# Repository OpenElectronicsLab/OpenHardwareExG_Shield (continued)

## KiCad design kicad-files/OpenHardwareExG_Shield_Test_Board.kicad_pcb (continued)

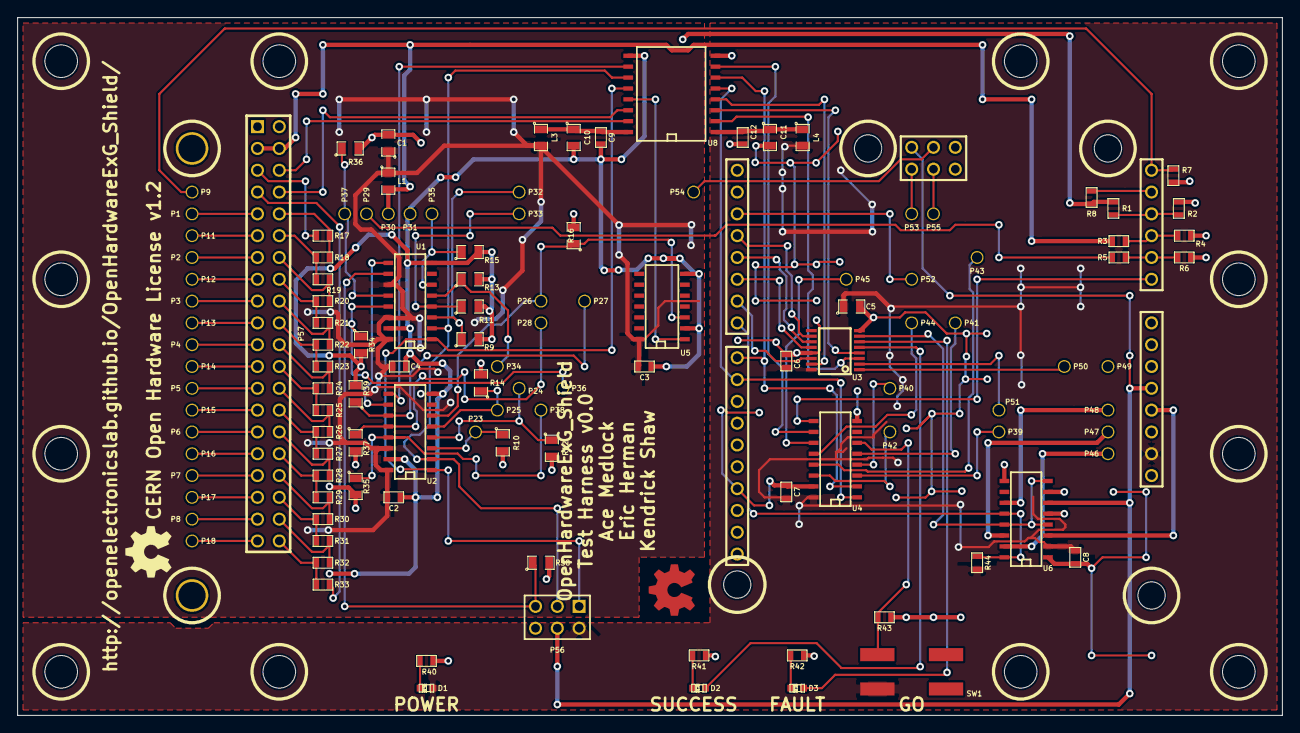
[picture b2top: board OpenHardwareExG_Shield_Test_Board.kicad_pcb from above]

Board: 4 copper layers, 147.3 x 81.3 mm, 137 parts (0 on the bottom side), 105 nets.

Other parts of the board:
Hole_M3, Hole_M3#2, Hole_M3#3, Hole_M3#4, Hole_M3#5, Hole_M3#6, Hole_M3#7, Hole_M3#8, Hole_M3#9, Hole_M3#10, Hole_M3#11, Hole_M3#12, Hole_M3#13, Hole_M3#14: VAL**; Hole_M3

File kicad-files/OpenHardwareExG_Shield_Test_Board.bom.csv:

ref,value,footprint,partnum,supplier
C1,10uF,SM0805,LMK212B7106KG-TD,mouser
C2,100nF,SM0603,VJ0603Y104JXJPW1BC,mouser
C3,100nF,SM0603,VJ0603Y104JXJPW1BC,mouser
C4,100nF,SM0603,VJ0603Y104JXJPW1BC,mouser
C5,10uF,SM0805,LMK212B7106KG-TD,mouser
C6,100nF,SM0603,VJ0603Y104JXJPW1BC,mouser
C7,100nF,SM0603,VJ0603Y104JXJPW1BC,mouser
C8,100nF,SM0603,VJ0603Y104JXJPW1BC,mouser
C9,100nF,SM0603,VJ0603Y104JXJPW1BC,mouser
C10,10uF,SM0805,LMK212B7106KG-TD,mouser
C11,10uF,SM0805,LMK212B7106KG-TD,mouser
C12,100nF,SM0603,VJ0603Y104JXJPW1BC,mouser
D1,LED,LED-0603,HT-193UYG-5592,mouser
D2,LED,LED-0603,HT-193UYG-5592,mouser
D3,LED,LED-0603,APTD1608SURCK,mouser
L1,MH2029-221Y,SM0805,MH2029-221Y,mouser
L3,MH2029-221Y,SM0805,MH2029-221Y,mouser
L4,MH2029-221Y,SM0805,MH2029-221Y,mouser
P1,CONN_1,POGO_PIN_BASE,PRT-09173,sparkfun
P2,CONN_1,POGO_PIN_BASE,PRT-09173,sparkfun
P3,CONN_1,POGO_PIN_BASE,PRT-09173,sparkfun
P4,CONN_1,POGO_PIN_BASE,PRT-09173,sparkfun
P5,CONN_1,POGO_PIN_BASE,PRT-09173,sparkfun
P6,CONN_1,POGO_PIN_BASE,PRT-09173,sparkfun
P7,CONN_1,POGO_PIN_BASE,PRT-09173,sparkfun
P8,CONN_1,POGO_PIN_BASE,PRT-09173,sparkfun
P9,CONN_1,POGO_PIN_BASE,PRT-09173,sparkfun
P11,CONN_1,POGO_PIN_BASE,PRT-09173,sparkfun
P12,CONN_1,POGO_PIN_BASE,PRT-09173,sparkfun
P13,CONN_1,POGO_PIN_BASE,PRT-09173,sparkfun
P14,CONN_1,POGO_PIN_BASE,PRT-09173,sparkfun
P15,CONN_1,POGO_PIN_BASE,PRT-09173,sparkfun
P16,CONN_1,POGO_PIN_BASE,PRT-09173,sparkfun
P17,CONN_1,POGO_PIN_BASE,PRT-09173,sparkfun
P18,CONN_1,POGO_PIN_BASE,PRT-09173,sparkfun
P19a,CONN_40x1,arduino_shield_with_holes_header,PRT-00116,sparkfun
P19b,CONN_3x2,arduino_shield_with_holes_spi,PRT-13010,sparkfun
P23,CONN_1,POGO_PIN_BASE,PRT-09173,sparkfun
P24,CONN_1,POGO_PIN_BASE,PRT-09173,sparkfun
P25,CONN_1,POGO_PIN_BASE,PRT-09173,sparkfun
P26,CONN_1,POGO_PIN_BASE,PRT-09173,sparkfun
P27,CONN_1,POGO_PIN_BASE,PRT-09173,sparkfun
P28,CONN_1,POGO_PIN_BASE,PRT-09173,sparkfun
P29,CONN_1,POGO_PIN_BASE,PRT-09173,sparkfun
P30,CONN_1,POGO_PIN_BASE,PRT-09173,sparkfun
P31,CONN_1,POGO_PIN_BASE,PRT-09173,sparkfun
P32,CONN_1,POGO_PIN_BASE,PRT-09173,sparkfun
P33,CONN_1,POGO_PIN_BASE,PRT-09173,sparkfun
P34,CONN_1,POGO_PIN_BASE,PRT-09173,sparkfun
P35,CONN_1,POGO_PIN_BASE,PRT-09173,sparkfun
P36,CONN_1,POGO_PIN_BASE,PRT-09173,sparkfun
P37,CONN_1,POGO_PIN_BASE,PRT-09173,sparkfun
P38,CONN_1,POGO_PIN_BASE,PRT-09173,sparkfun
P39,CONN_1,POGO_PIN_BASE,PRT-09173,sparkfun
P40,CONN_1,POGO_PIN_BASE,PRT-09173,sparkfun
P41,CONN_1,POGO_PIN_BASE,PRT-09173,sparkfun
P42,CONN_1,POGO_PIN_BASE,PRT-09173,sparkfun
P43,CONN_1,POGO_PIN_BASE,PRT-09173,sparkfun
P44,CONN_1,POGO_PIN_BASE,PRT-09173,sparkfun
P45,CONN_1,POGO_PIN_BASE,PRT-09173,sparkfun
P46,CONN_1,POGO_PIN_BASE,PRT-09173,sparkfun
P47,CONN_1,POGO_PIN_BASE,PRT-09173,sparkfun
P48,CONN_1,POGO_PIN_BASE,PRT-09173,sparkfun
P49,CONN_1,POGO_PIN_BASE,PRT-09173,sparkfun
P50,CONN_1,POGO_PIN_BASE,PRT-09173,sparkfun
P51,CONN_1,POGO_PIN_BASE,PRT-09173,sparkfun
P52,CONN_1,POGO_PIN_BASE,PRT-09173,sparkfun
P53,CONN_1,POGO_PIN_BASE,PRT-09173,sparkfun
P54,CONN_1,POGO_PIN_BASE,PRT-09173,sparkfun
P55,CONN_1,POGO_PIN_BASE,PRT-09173,sparkfun
P56,CONN_3X2,pin_array_3x2,PRT-12807,sparkfun
P57,CONN_20X2,PIN_ARRAY_20X2,571-2-826925-0,mouser
R1,10k,SM0603,RR0816P-103-D,mouser
R2,1k,SM0603,CRCW06031K00FKEA,mouser
R3,10k,SM0603,RR0816P-103-D,mouser
R4,1k,SM0603,CRCW06031K00FKEA,mouser
R5,10k,SM0603,RR0816P-103-D,mouser
R6,1k,SM0603,CRCW06031K00FKEA,mouser
R7,5.1k,SM0603,CRCW06035K10FKEA,mouser
R8,100,SM0603,CRCW0603100RFKEA,mouser
R9,1M,SM0805,RR1220P-105-D,mouser
R10,1M,SM0805,RR1220P-105-D,mouser
R11,1M,SM0805,RR1220P-105-D,mouser
R12,1M,SM0805,RR1220P-105-D,mouser
R13,1M,SM0805,RR1220P-105-D,mouser
R14,1M,SM0805,RR1220P-105-D,mouser
R15,1M,SM0805,RR1220P-105-D,mouser
R16,1M,SM0805,RR1220P-105-D,mouser
R17,15k,SM0603,MCT06030C1502FP500,mouser
R18,100,SM0603,CRCW0603100RFKEA,mouser
R19,100,SM0603,CRCW0603100RFKEA,mouser
R20,100,SM0603,CRCW0603100RFKEA,mouser
R21,100,SM0603,CRCW0603100RFKEA,mouser
R22,100,SM0603,CRCW0603100RFKEA,mouser
R23,100,SM0603,CRCW0603100RFKEA,mouser
R24,100,SM0603,CRCW0603100RFKEA,mouser
R25,100,SM0603,CRCW0603100RFKEA,mouser
R26,100,SM0603,CRCW0603100RFKEA,mouser
R27,100,SM0603,CRCW0603100RFKEA,mouser
R28,100,SM0603,CRCW0603100RFKEA,mouser
R29,100,SM0603,CRCW0603100RFKEA,mouser
R30,100,SM0603,CRCW0603100RFKEA,mouser
R31,100,SM0603,CRCW0603100RFKEA,mouser
R32,100,SM0603,CRCW0603100RFKEA,mouser
R33,15k,SM0603,MCT06030C1502FP500,mouser
R34,1M,SM0805,RR1220P-105-D,mouser
R35,1M,SM0805,RR1220P-105-D,mouser
R36,1M,SM0805,RR1220P-105-D,mouser
R37,1M,SM0805,RR1220P-105-D,mouser
R38,1M,SM0805,RR1220P-105-D,mouser
R39,1M,SM0805,RR1220P-105-D,mouser
R40,560,SM0603,MCT06030C5600FP500,mouser
R41,560,SM0603,MCT06030C5600FP500,mouser
R42,560,SM0603,MCT06030C5600FP500,mouser
R43,10k,SM0603,RR0816P-103-D,mouser
R44,10k,SM0603,RR0816P-103-D,mouser
SW1,SW_PUSH,smt-tactile-button,B3SN-3012P,mouser
U1,74HC165,SO16E,SN74HC165DR,mouser
U2,74HC165,SO16E,SN74HC165DR,mouser
U3,74HC595PWR,TSSOP16,SN74HC595PWR,mouser
U4,74HC165,SO16E,SN74HC165DR,mouser
U5,74LS125,SO14E,SN74LS125AD,mouser
U6,TPS2095D,SO16E,TPS2095D,mouser
U8,SI8661,SO16W,Si8661BD-B-IS,mouser

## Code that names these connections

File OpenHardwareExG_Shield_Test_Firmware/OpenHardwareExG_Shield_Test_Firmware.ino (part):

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		simulate_board_below = 0;
		master_i_cs = 1;
		slave_i_cs = 1;
		signal_a = 0;
		signal_b = 0;
		success_led = 0;
		fault_led = 0;
		enable_shield = 1;
	}

	static ShiftOutputs power_off()
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		ShiftOutputs result;
		result.master_i_cs = 0;
		result.slave_i_cs = 0;
		result.enable_shield = 0;

		return result;
	}
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	unsigned dout_iso:1;
	unsigned unused1:1;

	unsigned gpio1:1;
	unsigned gpio2:1;
	unsigned gpio3:1;
	unsigned gpio4:1;
	unsigned daisyin:1;
	unsigned biasinv:1;
	unsigned unused2:1;
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};

enum Pins {
	PIN_SHIFT_IN = A0,
	PIN_DIV_VIN_ISO = A1,
	PIN_DIV_3V3_ISO = A2,
	PIN_DIV_GND_ISO = A3,
	PIN_RESIST_GND_ISO = A4,
	PIN_BIASOUT_FILT = A5,

	IPIN_MASTER_DRDY = 2,
	IPIN_SHIFT_OUT_SRCLR = 3,
	PIN_SHIFT_OUT_SRCLK = 4,
	PIN_SHIFT_OUT_RCLK = 5,
	PIN_SHIFT_OUT = 6,
	IPIN_SHIELD_SHORTED = 7,
	PIN_SHIFT_CLK = 8,
	IPIN_SHIFT_SH_LD = 9,
};

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
void shift_out(bool value)
{
	digitalWrite(PIN_SHIFT_OUT_SRCLK, LOW);	// should be a NOP
	digitalWrite(PIN_SHIFT_OUT, value ? HIGH : LOW);
	delayMicroseconds(shift_clock_delay);
	digitalWrite(PIN_SHIFT_OUT_SRCLK, HIGH);
	delayMicroseconds(shift_clock_delay);
	digitalWrite(PIN_SHIFT_OUT_SRCLK, LOW);
}

void write_shift_out(const struct ShiftOutputs &output)
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	shift_out(output.signal_a);
	shift_out(output.slave_i_cs);
	shift_out(output.master_i_cs);
	shift_out(output.simulate_board_below ? 0 : 1);	// IPIN ~SEND_TO_GND~_MASTER

	digitalWrite(PIN_SHIFT_OUT_RCLK, HIGH);
	delayMicroseconds(shift_clock_delay);
	digitalWrite(PIN_SHIFT_OUT_RCLK, LOW);
}

unsigned shift_in()
{
	unsigned d = digitalRead(PIN_SHIFT_IN);
	digitalWrite(PIN_SHIFT_CLK, HIGH);
	delayMicroseconds(shift_clock_delay);
	digitalWrite(PIN_SHIFT_CLK, LOW);
	delayMicroseconds(shift_clock_delay);
	return d;
}
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	input.i_drdy_iso = shift_in();
	input.dout_iso = shift_in();

	input.gpio4 = shift_in();
	input.gpio3 = shift_in();
	input.gpio2 = shift_in();
	input.gpio1 = shift_in();
	input.unused2 = shift_in();
	input.daisyin = shift_in();
	input.biasinv = shift_in();
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	// initialize digital pin 13 as an output.
	pinMode(13, OUTPUT);

	pinMode(PIN_SHIFT_IN, INPUT);
	pinMode(PIN_SHIFT_CLK, OUTPUT);
	pinMode(IPIN_SHIFT_SH_LD, OUTPUT);

	pinMode(PIN_DIV_VIN_ISO, INPUT);	// un-needed?
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	pinMode(PIN_RESIST_GND_ISO, OUTPUT);
	pinMode(IPIN_SHIELD_SHORTED, INPUT);

	pinMode(PIN_BIASOUT_FILT, INPUT);
	pinMode(IPIN_MASTER_DRDY, INPUT);

	// set up the pins for the output shift registers
	pinMode(PIN_SHIFT_OUT_RCLK, OUTPUT);
	pinMode(PIN_SHIFT_OUT_SRCLK, OUTPUT);
	pinMode(PIN_SHIFT_OUT, OUTPUT);
	pinMode(IPIN_SHIFT_OUT_SRCLR, OUTPUT);

	digitalWrite(IPIN_SHIFT_OUT_SRCLR, HIGH);
	digitalWrite(PIN_SHIFT_OUT_RCLK, LOW);

	// init shift-in pins
	digitalWrite(IPIN_SHIFT_SH_LD, HIGH);
	digitalWrite(PIN_SHIFT_CLK, LOW);

	// zero the shift-out (including enable_shield=0)
	ShiftOutputs output = ShiftOutputs::power_off();
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
	for (int i = 0; i < 10 /* or board removed */ ; ++i) {
		for (unsigned j = 0; j < err.blink_code; ++j) {
			errorOutput.fault_led = 0;
			write_shift_out(errorOutput);
			if (delay_or_go_button(200)) {
				goto EXIT_BLINK_ERROR;
			}
			errorOutput.fault_led = 1;
			write_shift_out(errorOutput);
			if (delay_or_go_button(300)) {
				goto EXIT_BLINK_ERROR;
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	}

EXIT_BLINK_ERROR:
	errorOutput.fault_led = 0;
	write_shift_out(errorOutput);
}

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	}
	++i;

	if (expected->gpio1 != actual->gpio1) {
		errors |= (1L << i);
		sprintf(buf, fmt, "gpio1", expected->gpio1, actual->gpio1);
		Serial.println(buf);
	}
	++i;
	if (expected->gpio2 != actual->gpio2) {
		errors |= (1L << i);
		sprintf(buf, fmt, "gpio2", expected->gpio2, actual->gpio2);
		Serial.println(buf);
	}
	++i;
	if (expected->gpio3 != actual->gpio3) {
		errors |= (1L << i);
		sprintf(buf, fmt, "gpio3", expected->gpio3, actual->gpio3);
		Serial.println(buf);
	}
	++i;
	if (expected->gpio4 != actual->gpio4) {
		const char *msg;
		if (BROKEN_GPIO4) {
			msg = skip;
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			msg = fmt;
			errors |= (1L<<i);
		}
		sprintf(buf, msg, "gpio4", expected->gpio4, actual->gpio4);
		Serial.println(buf);
	}
	++i;
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{
	{
		ShiftOutputs output = ShiftOutputs::power_off();
		output.enable_shield = 1;
		write_shift_out(output);
	}

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	}

	ShiftInputs default_expected;
	default_expected.slave_and_slave_cs = 0;
	default_expected.master_and_master_cs = 0;
	default_expected.i_master = 0;
	default_expected.master = 1;
	default_expected.go_button = 0;
	default_expected.i_cs = 1;
	default_expected.dout = 0;
	default_expected.i_drdy = 1;
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	default_expected.mosi_iso = 0;
	default_expected.sclk_iso = 0;
	default_expected.i_cs_iso = 1;
	default_expected.master_iso = 1;
	default_expected.clk_iso = 0;
	default_expected.i_drdy_iso = 1;
	default_expected.dout_iso = 0;
	default_expected.unused1 = 0;

	default_expected.gpio1 = 0;
	default_expected.gpio2 = 0;
	default_expected.gpio3 = 0;
	default_expected.gpio4 = 0;
	default_expected.daisyin = 0;
	default_expected.biasinv = 0;
	default_expected.unused2 = 0;

	// TODO: compare both shift inputs and SPI inputs
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
		delayMicroseconds(DIGITAL_STATE_CHANGE_DELAY_MICROS);
		ShiftInputs expected = default_expected;
		expected.master_and_master_cs = 1;
		expected.i_cs = 0;
		expected.i_cs_iso = 0;
		expected.dout = 1;
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
		delayMicroseconds(DIGITAL_STATE_CHANGE_DELAY_MICROS);
		ShiftInputs expected = default_expected;
		expected.master_and_master_cs = 1;
		expected.i_cs = 0;
		expected.i_cs_iso = 0;
		expected.dout = 1;
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
		delayMicroseconds(DIGITAL_STATE_CHANGE_DELAY_MICROS);
		ShiftInputs expected = default_expected;
		expected.slave_and_slave_cs = 1;
		expected.i_master = 1;
		expected.master = 0;
		expected.master_iso = 0;
		expected.i_cs = 0;
		expected.i_cs_iso = 0;

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		delayMicroseconds(DIGITAL_STATE_CHANGE_DELAY_MICROS);
		ShiftInputs expected = default_expected;
		expected.i_master = 1;
		expected.master = 0;
		expected.master_iso = 0;

		ShiftInputs actual = read_shift_in();
		bool compare_dout = false;
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
		delayMicroseconds(DIGITAL_STATE_CHANGE_DELAY_MICROS);
		ShiftInputs expected = default_expected;
		expected.slave_and_slave_cs = 1;
		expected.i_master = 1;
		expected.master = 0;
		expected.master_iso = 0;
		expected.i_cs = 0;
		expected.i_cs_iso = 0;

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
		delayMicroseconds(DIGITAL_STATE_CHANGE_DELAY_MICROS);
		ShiftInputs expected = default_expected;
		expected.slave_and_slave_cs = 1;
		expected.i_master = 1;
		expected.master = 0;
		expected.master_iso = 0;
		expected.i_cs = 0;
		expected.i_cs_iso = 0;

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	for (int i = 0; i < 4; ++i) {
		uint8_t data = (1 << (4 + i));
		if (BROKEN_GPIO4) {
			data |= 0x08;	// set gpio4 to be an input
		}
		adc_wreg(GPIO, data);

		ShiftInputs expected = default_expected;
		expected.master_and_master_cs = 1;
		expected.i_cs = 0;
		expected.i_cs_iso = 0;
		expected.mosi_iso = 1;
		switch (i) {
		case 0:
			expected.gpio1 = 1;
			break;
		case 1:
			expected.gpio2 = 1;
			break;
		case 2:
			expected.gpio3 = 1;
			break;
		case 3:
			expected.gpio4 = 1;
			break;
		}
		ShiftInputs actual = read_shift_in();
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		output.master_i_cs = 0;
		// input/ladder
		// A high, b low - read analog data, ensure in approx range
		output.signal_b = 1;
		write_shift_out(output);
	}
	// Power up the internal reference and wait for it to settle
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	}

	{
		int biasoutfilt = analogRead(PIN_BIASOUT_FILT);
		double one_volt = (1023.0/3.3);
		int max_expected = (int) (0.1 * one_volt);
		if (biasoutfilt > max_expected) {
			sprintf(buf, "PIN_BIASOUT_FILT: %d > %d",
				biasoutfilt, max_expected);
			Serial.println(buf);
			spi_teardown();
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	Serial.println("done waiting");

	{
		int biasoutfilt = analogRead(PIN_BIASOUT_FILT);
		double expected_2_5_volt = ((1023.0/3.3) * 2.5);
		int max_expected = (int) (1.1 * expected_2_5_volt);
		int min_expected = (int) (0.9 * expected_2_5_volt);
		if ((biasoutfilt > max_expected)
			|| (biasoutfilt < min_expected)) {
			sprintf(buf, "PIN_BIASOUT_FILT: %d outside %d - %d",
				biasoutfilt, min_expected, max_expected);
			Serial.println(buf);
			spi_teardown();
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	int a_vin = analogRead(PIN_DIV_VIN_ISO);
	int a_3v3 = analogRead(PIN_DIV_3V3_ISO);
	int a_gnd = analogRead(PIN_DIV_GND_ISO);
	int a_bia = analogRead(PIN_BIASOUT_FILT);

	char buf[1024];

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	Serial.println("");

	Serial.print("P32: ");
	Serial.print(input.gpio1);
	Serial.print(", P33: ");
	Serial.print(input.gpio2);
	Serial.print(", P34: ");
	Serial.print(input.gpio3);
	Serial.print(", P35: ");
	Serial.print(input.gpio4);
	Serial.print(", P36: ");
	Serial.print(input.daisyin);
	Serial.print(", P37: ");
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			} else {
				Serial.println("SUCCESS!");
				ShiftOutputs output;
				output.success_led = 1;

				write_shift_out(output);

				delay(3000);

				output.enable_shield = 0;
				write_shift_out(output);

				// in real life we'd loop until detected board removed
				delay(3000);
				output.success_led = 0;
				output.fault_led = 0;
				write_shift_out(output);
			}
		}
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
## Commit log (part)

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2014-08-30 init
2014-08-30 add CERN OHL v1.2 license
2014-08-30 added README
2014-08-30 initial rough schematic of the OpenHardwareExG_Shield
2014-09-27 added start of master/slave detection
2014-10-05 remove BIAS jumpers header
2014-10-11 tidy up wires
2014-10-11 remove filter bypass jumpers
2014-10-11 fix label MASTER -> MASTER_ISO
2014-10-11 connected DRDY, DOUT, and CS for MASTER and SLAVEs
2014-10-18 add more labels
2014-10-18 added capacitors for logic chips
    Also distinguish ARDUINO_VCC from filtered VCC
2014-10-18 isolated side of ADuM6000 hooked up
2014-10-18 non-isolated side of ADuM6000 hooked up
2014-10-18 add test points and NC unused pins
2014-10-18 fixed labels and ERC issues
2014-10-18 rough draft of a test shield
2014-10-25 added kicad symbols for 74HC595PWR and TPS2095D
2014-10-25 added test points for all I/O to the OpenHardwareExG_Shield
2014-10-25 Test_Board now uses all the test points for I/O to shield
2014-11-02 add pulldown resistors to pogo inputs
2014-11-02 added jumper block for input of calibration signals
2014-11-02 Clarify that all isolation on the test board is actually BOGUS
2014-11-08 fix some overlapping labels
2014-11-08 add non-isolated powerlines to test board test signal header
2014-11-08 starting to choose footprints
2014-11-08 add footprints for SMD headers and pogopads
2014-11-08 add pogo-pin base footprints to test board
2014-11-09 remove some backup and cache files
2014-11-09 filled out footprints for remaining test board parts
2014-11-30 add footprints to schematics
2014-11-30 update notes, footprints on schematic
2014-11-30 first cut at a 1299 version of a BOM
2014-12-13 add components to kicad_pcb
2014-12-14 start actually laying out the board
    Added a 0 Ohm resistor to clarify the star-grounding of AGND and DGND,
    we will likely remove this later.
2015-01-03 checkpoint: untangle isolated/non-isolated rats-nest
    Also, remove resistors from data lines which are now short.
2015-01-03 checkpoint: layout analog capacitors
2015-01-03 east and south sides of ADS1299 mostly connected
2015-01-10 initial layout of filter resistors and capacitors
2015-01-10 connect filter to ADS
2015-01-10 wired up most of power
2015-01-18 move GPIO north, begin to cinch-in south end footprints
2015-01-18 lay tracks for south end
2015-01-25 add footprint for PIN_ARRAY_7x1
2015-01-25 place GPIO PINS and digital test-points
2015-01-25 move regulator north of power isolator
2015-02-07 add 18x1 connector
2015-02-07 switch EEG header from 2-row to 18x1 row
2015-02-07 place EEG header and testpoints
2015-02-07 connect the EEG inputs to the chip, via the filter
2015-02-07 sketch placement of pre-isolated logic
2015-02-07 ground planes on isolated side of board
2015-02-07 start to lay out power planes
2015-02-14 power planes finished on isolated side
2015-02-14 first cut at non-isolated side of board
2015-02-14 design rules check passes on board file
2015-02-14 add fiducial marks
2015-02-14 addeddrill holes; adjustments needed
2015-02-14 trying to improve the kicad arduino header mod file
2015-02-14 tweak a bit more, we need an official source
2015-02-14 we need to re-draw power planes next
2015-02-21 matched pin locations to kicad numbers in converted eagle file
    eagle:
    http://arduino.cc/en/Main/ArduinoBoardUno
    converted with:
    https://github.com/DanChianucci/Eagle2Kicad
2015-02-21 add a arduino_shield_with_holes drilled module
2015-02-21 using newer arduino_shield_with_holes footprint
    pins now in better location
2015-03-01 new board edges, pin alignment, labels
2015-03-01 TODO
2015-03-07 Moved labels out from underneath components
2015-03-07 tidy some labels
2015-03-07 tidy back labels, add no-mans lines
2015-03-07 the TI TPS2095D datasheet suggests "shield shorted" should be inverted
2015-03-07 inital testpoints, pre-pogo
2015-03-07 renumber pogo-points to have same Px as main board test points
2015-03-07 move pads to top side of board
2015-03-07 swap-in pogo-pins for pads
2015-03-07 checkpoint tesh-harness pcb, components separated
2015-03-07 re-order signal ladder for easier physical layout
2015-03-07 untangle the rats nest some
2015-03-07 we are doing it
2015-03-14 move connectors onto .1 grid
2015-03-14 power chips on isolated side of test harness from the board under test
2015-03-14 routing of test harness half done
2015-03-21 finish initial routing of the test board
2015-03-21 improve routing of ground and power; improve planes on BOGUS_ISO side
2015-03-21 update TODO
2015-03-28 improved routing and planes on test board
2015-03-28 move some labels
2015-03-28 make component values invisible on silk
2015-03-28 move some lables
2015-03-28 finish labels on test board
2015-03-28 adjust labels on main board
2015-04-11 add the first riser board of test harness
2015-04-11 add top riser board (with tabs) of test harness
2015-04-11 add a stub gh-pages
2015-04-11 silk screen for main board done
2015-04-18 add ground zone fills top and bottom; add bottom silk text
2015-04-18 notch-out ground zone to ensure AGND+DGND star-ground
2015-04-18 add gerber files
2015-04-18 fix schematic text to refer to correct resistor
2015-04-18 update BOM
2015-04-25 add rev. 0.0 to silk screen
2015-04-25 replace triac, new manufacture part number does not include a comma
2015-04-25 split BOMs into through-hole and surface-mount BOMs
2015-05-02 add addition text and CERN OHL logos (on copper layer, too)
2015-05-02 add extra set of tabs
2015-05-02 all test-harness boards on one panel
2015-05-02 gerbers for test-harness
2015-05-02 BOM for Test_Board
2015-05-23 VCAP capacitors do not match datasheet, but work fine for us.
2015-06-07 Start on firmware for shield test board
2015-06-13 enumerate Pogos and remaining Arduino PIN values
2015-06-13 initalize the remaining IN and OUT pins we expect to use in setup()
    and simplify the shift-out initialization by simply not clearing, yet
    allowing the first run of the loop() to shift meaningful data out
2015-06-13 send some output to "blink" Serial, too
2015-07-26 fix PWRDWN and RESET: tie HIGH not LOW. D'oh!
2015-07-26 notes regarding prototype board errors
2015-08-01 ADS129x pins tied high should tie to 3.3V_ISO (not VIN_ISO)
2015-08-01 fixup PCB to tie ~PWDN~ and ~RESET~ to 3.3V_ISO
2015-08-01 fix the crowbar on schematic
    PCB still needs fixing
2015-08-14 add footprint to 330uF C73
2015-08-14 just drop C73 on the pcb, will need layout work
2015-08-30 T49D337K010ATE150 is a "D" footprint, not "E"
2015-08-30 add note to recommend female header for GPIO (P22)
2015-08-30 add C73 (330uF) to PCB
2015-08-30 version bump to r0.1
2015-08-30 move via for C73 to the power plane
2015-08-30 rev 0.1 gerbers
2015-08-30 Update drill report files
2015-08-30 sketch of rev_0.1 bom
2015-08-30 note the need to fix footprint
2015-08-30 should just be date updates
2015-08-30 fix C43 footprint
2015-09-13 fix outputs for signalA,B and simulateBoardBelow
2015-09-13 sketch in reading input
2015-09-13 better debug printing
2015-09-13 drive A4 (GND_BOGUS_ISO)
2015-09-13 update our TODO for test harness work
2015-09-13 cheesy Makefile to use Arduino-1.6 commandline build
2015-09-18 checkpoint reading from shift-in
2015-09-18 output shiftin to Serial
2015-09-18 print out the unused shift data
2015-09-18 notes about shift-in debugging
2015-09-27 first bit of shift-in is available after load, before first clock
2015-09-27 move the hardware validation code out of main loop
2015-09-27 first sample test code
2015-09-27 updated TODO
2015-10-03 init the PIN_SHIFT_OUT_RCLK low
2015-10-03 break-out tests as separate function
2015-10-03 do not apply solder to POGO_PAD test points
2015-10-18 updated TODO, including shortcomings we plan to ignore
2015-11-15 these TODO items are done
2015-11-15 working test detecting 5V shorted to GND
2015-11-15 skeleton for checking 3v3
2015-12-05 add the *-cache.lib files for forward compatibility
2015-12-05 move the "loop" function to end of file
    loop() calls harness_hardware_validation() which was
    defined below it, now defined above
2015-12-05 delay before checking for short; allow capacitors to charge
2015-12-05 connect DGND_ISO to DGND (DOH!); convert to KiCad 4
2015-12-11 finish check for 3v3_BOGUS_ISO
2015-12-11 add check for VIN_ISO
2015-12-11 add additional delay between checking for short and checking voltage
2015-12-11 drive RESIST_GND_ISO high and low (and check)
2015-12-20 check initial state
2015-12-20 checking master CS
2016-01-14 test slave CS and neither
2016-01-14 sketch in simulating board bellow
2016-01-24 replace fudicial marks with new library modules
    removes the paste layer
    also added fudicials to the back
    and one near the ADS129x
2016-01-24 move sucess/failure reporting outside of the test loop
2016-01-24 add test for simulate board below; refactor default states
2016-01-24 add test for simulate board below and slave selected
2016-01-24 add test for simulate board below and slave and master selected
2016-01-24 actually blink the blink_code
2016-01-24 break early from blink_error if "go" button is pressed
2016-03-13 add test for MOSI/MOSI_iso
2016-03-13 add a SCLK test
2016-03-13 use SPI, check chip ID from ADS1299
2016-03-13 extract SPI setup and teardown functions
2016-03-13 add some GPIO testing
2016-03-20 fix GPIO3 error
2016-03-20 test for DRDY and read a frame from ADS and test for "Magic"
2016-03-20 turn the inputs on and look at values
    seems that some are wrong, investigate next time
2016-03-21 try to fixup whitespace and make naming more consistent
2016-03-21 pull in the ads1298.h from OpenHardwareExG
    we are using the ADS1299, so some values are not the same ...
    we will need to fix that eventually ....
2016-03-27 remove duplication
2016-03-27 finished first channel input sanity check
2016-03-27 tidy up some names
2016-04-02 make measurement tollerace compile-time configurable
2016-04-02 add notes about connecting test points for next rev
2016-04-02 sketch out testing plan for IN1P..IN8N
2016-04-07 add test for shorts between pins of adjacent channels
2016-04-07 reset channels, sketch next test
2016-04-07 add the first BIAS OUT check
2016-05-01 contribution notes
2016-05-15 BIASOUT tested
2016-05-15 remove skip of GPIO4
2016-05-15 testing DRDY toggle - something not right
    added back the skip of GPIO4
2016-05-29 default GPIO4 to not be broken
2016-06-04 bump PCB version to 0.2
2016-06-04 add expected v0.2 GoldPhoenix BOM
2016-07-17 pcb v0.2.1: fix text alignement of multi-line text
    It seems that the switch to KiCAD v4 may have changed
    the way multi-line text items are aligned on PCBs.
    This converts all multi-line to multiple single line items.
2016-07-17 remove gerbers for rev 0.2, they contained silkscreen errors
2016-07-17 sticker to fix silk alignment on v0.2
2016-07-17 make note about test harness redesign work
2016-07-17 order placed
2016-07-23 add POGO_HEAD_HOLE and update "connectors" library to kicad v4
2016-07-23 expand test jig board to stabilize pogo pins
2016-07-23 gerbers for new test harness reiser board
2016-08-25 DRDY seems not to return to expected state
2016-08-30 add pulldown resistors for GPIOs
2016-09-04 add label to Arduino header pins 5, 6, and 7
2016-09-04 adjust label locations
2016-12-03 update text
    remove text "this project is in early development and not ready for use"
2017-06-24 move test harness ancillary files to ancillary-files-test-harness
2017-06-24 adding Gerber and drill files
2017-07-28 rename test harness firmware directory with clearer name
2017-07-28 move Test_Harness files into their own clearly separate directory
2017-07-28 adjust for new version of KiCAD, copy in lib from main project
2017-07-28 CERN OHL v1.2
2017-07-28 add link to OpenHardwareExG_Shield_Arduino_Library
